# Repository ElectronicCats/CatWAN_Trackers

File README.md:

# LoRa CatTrack Zero

Electronic Cats invests time and resources providing this open source design, please support Electronic Cats and open-source hardware by purchasing products from Electronic Cats!

Designed by Electronic Cats.

Hardware released under an CERN Open Hardware Licence v1.2. See the LICENSE_HARDWARE file for more information.

Electronic Cats is a registered trademark, please do not use if you sell these PCBs.

26 Nov 2018

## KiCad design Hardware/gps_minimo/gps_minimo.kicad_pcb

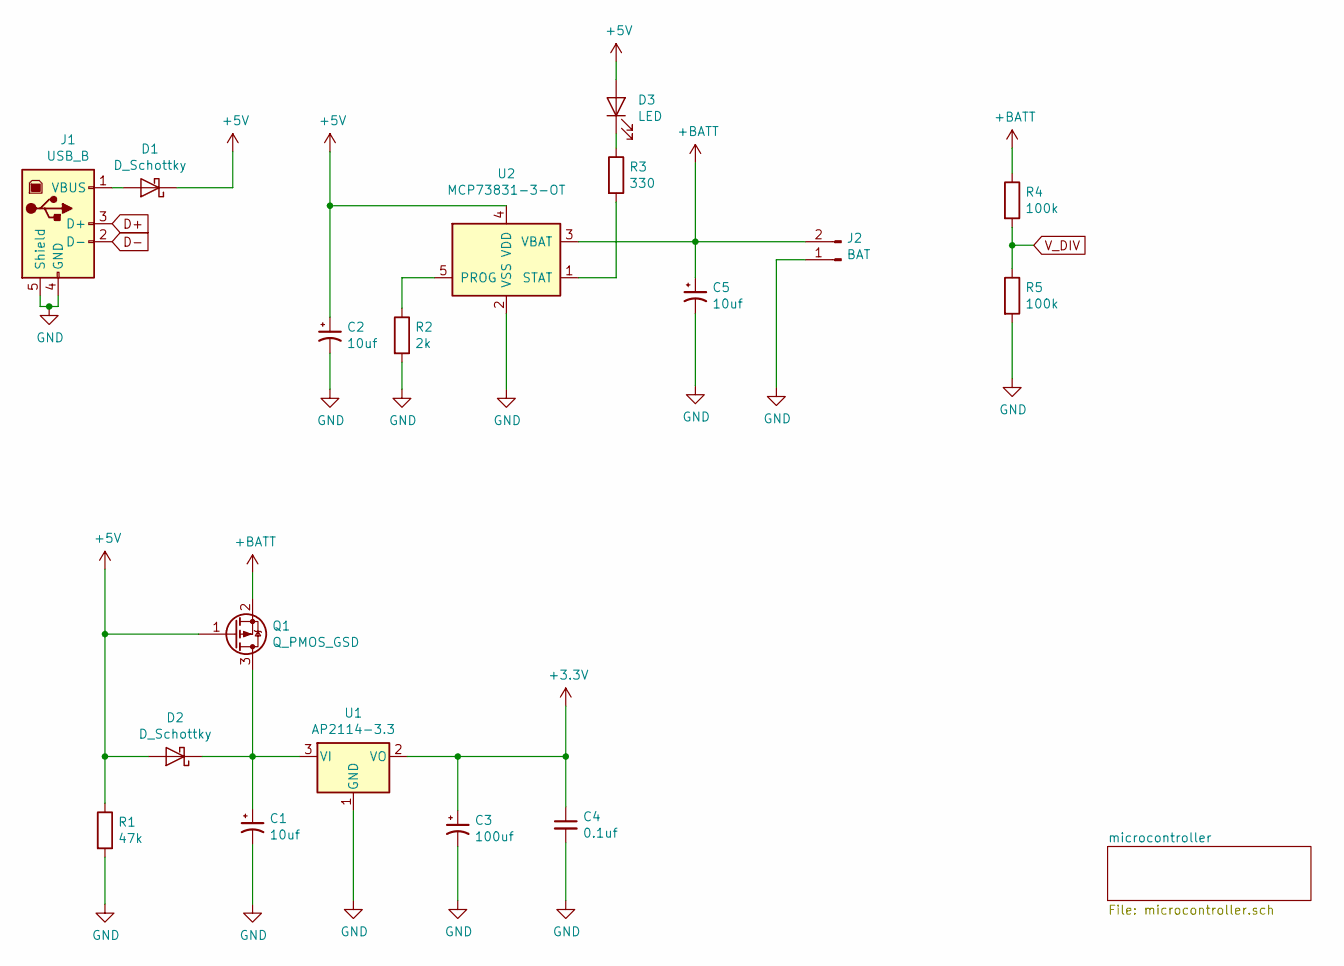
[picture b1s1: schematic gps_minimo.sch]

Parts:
C1, C2, C5: 10uf; C_1206_3216Metric_Pad1.42x1.75mm_HandSolder
C3: 100uf; C_1206_3216Metric_Pad1.42x1.75mm_HandSolder
C4: 0.1uf; C_1206_3216Metric_Pad1.42x1.75mm_HandSolder
D1, D2: D_Schottky; D_SOD-123
D3: LED; LED_1206_3216Metric_Pad1.42x1.75mm_HandSolder
J1: USB_B; USB_Micro-B_Wuerth_629105150521
J2: BAT; PinHeader_1x02_P2.54mm_Vertical
Q1: Q_PMOS_GSD; SOT-23
R1: 47k; R_1206_3216Metric_Pad1.42x1.75mm_HandSolder
R2: 2k; R_1206_3216Metric_Pad1.42x1.75mm_HandSolder
R3: 330; R_1206_3216Metric_Pad1.42x1.75mm_HandSolder
R4, R5: 100k; R_1206_3216Metric_Pad1.42x1.75mm_HandSolder
U1: AP2114-3.3; SOT-223-3_TabPin2
U2: MCP73831-3-OT; SOT-23-5

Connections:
+3V3: C3.1, C4.1, U1.2 (VO); also elsewhere on the board
+5V: C2.1, D1.1 (K), D2.2 (A), D3.2 (A), Q1.1 (G), R1.1, U2.4 (VDD)
+BATT: C5.1, J2.2, Q1.2 (S), R4.1, U2.3 (VBAT)
D+: J1.3 (D+); also elsewhere on the board
D-: J1.2 (D-); also elsewhere on the board
GND: C1.2, C2.2, C3.2, C4.2, C5.2, J1.4 (GND), J1.5 (Shield), J2.1, R1.2, R2.2, R5.2, U1.1 (GND), U2.2 (VSS); also elsewhere on the board
unnamed: C1.1, D2.1 (K), Q1.3 (D), U1.3 (VI)
unnamed: D1.2 (A), J1.1 (VBUS)
unnamed: D3.1 (K), R3.1
unnamed: R2.1, U2.5 (PROG)
unnamed: R3.2, U2.1 (STAT)
V_DIV: R4.2, R5.1; also elsewhere on the board

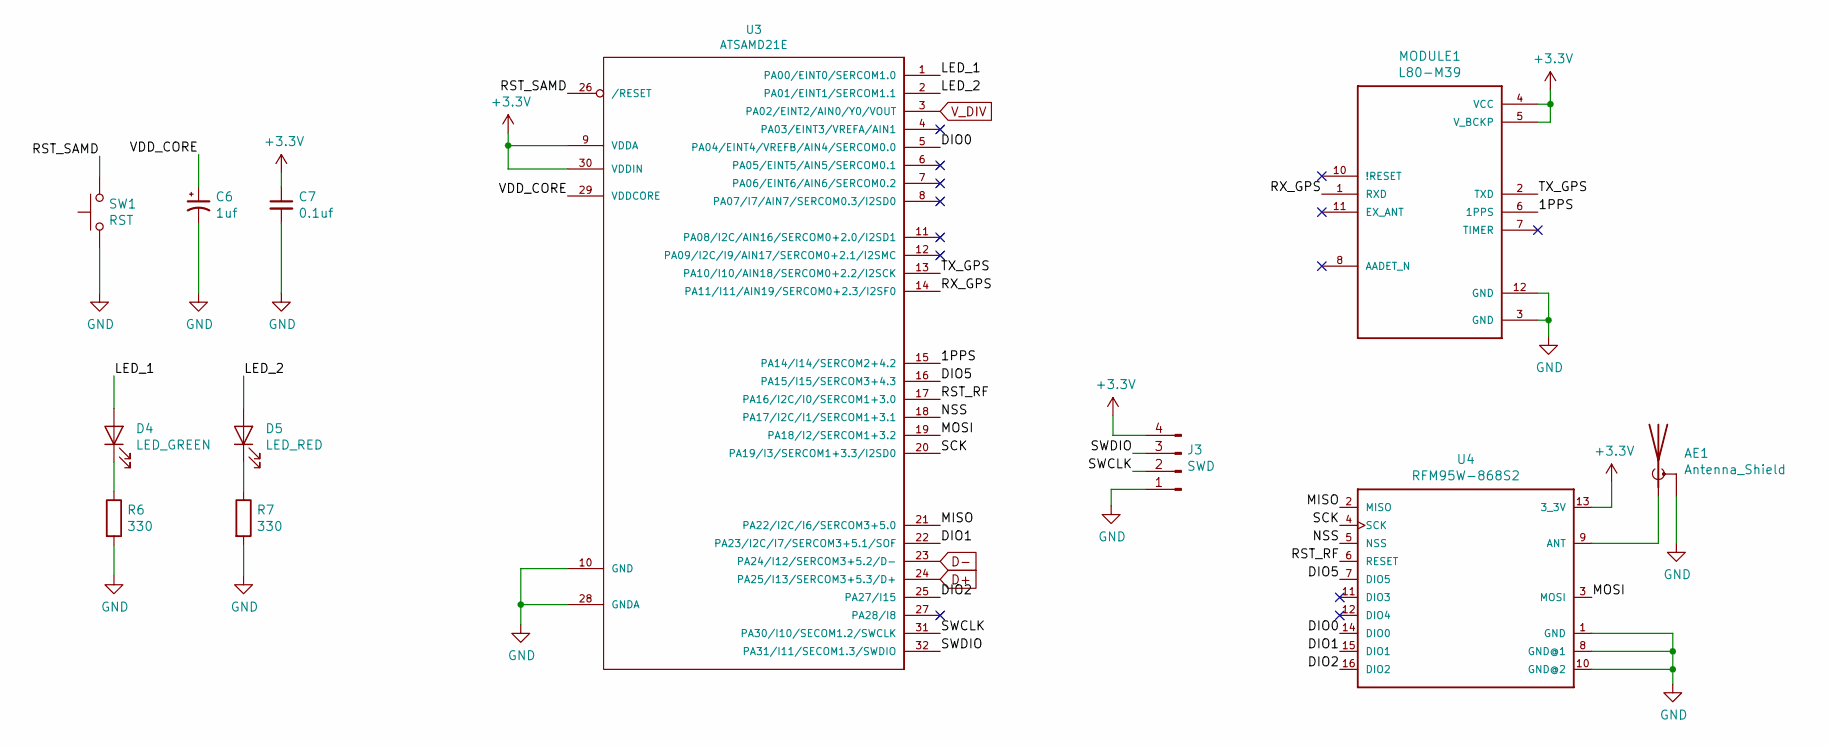
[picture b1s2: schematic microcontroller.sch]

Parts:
AE1: Antenna_Shield; MOLEX_1661
C6: 1uf; C_1206_3216Metric_Pad1.42x1.75mm_HandSolder
C7: 0.1uf; C_1206_3216Metric_Pad1.42x1.75mm_HandSolder
D4: LED_GREEN; LED_1206_3216Metric_Castellated
D5: LED_RED; LED_1206_3216Metric_Castellated
J3: SWD; PinHeader_1x04_P2.54mm_Vertical
MODULE1: L80-M39; QUECTEL_L80-M39
R6, R7: 330; R_1206_3216Metric_Pad1.42x1.75mm_HandSolder
SW1: RST; SW_SPST_TL3342
U3: ATSAMD21E; TQFP-32_7x7mm_P0.8mm
U4: RFM95W-868S2; RFM95W

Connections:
+3V3: C7.1, J3.4, MODULE1.4 (VCC), MODULE1.5 (V_BCKP), U3.9 (VDDA), U3.30 (VDDIN), U4.13 (3_3V); also elsewhere on the board
/microcontroller/1PPS: MODULE1.6 (1PPS), U3.15 (PA14/I14/SERCOM2+4.2)
/microcontroller/DIO0: U3.5 (PA04/EINT4/VREFB/AIN4/SERCOM0.0), U4.14 (DIO0)
/microcontroller/DIO1: U3.22 (PA23/I2C/I7/SERCOM3+5.1/SOF), U4.15 (DIO1)
/microcontroller/DIO2: U3.25 (PA27/I15), U4.16 (DIO2)
/microcontroller/DIO5: U3.16 (PA15/I15/SERCOM3+4.3), U4.7 (DIO5)
/microcontroller/LED_1: D4.2 (A), U3.1 (PA00/EINT0/SERCOM1.0)
/microcontroller/LED_2: D5.2 (A), U3.2 (PA01/EINT1/SERCOM1.1)
/microcontroller/MISO: U3.21 (PA22/I2C/I6/SERCOM3+5.0), U4.2 (MISO)
/microcontroller/MOSI: U3.19 (PA18/I2/SERCOM1+3.2), U4.3 (MOSI)
/microcontroller/NSS: U3.18 (PA17/I2C/I1/SERCOM1+3.1), U4.5 (NSS)
/microcontroller/RST_RF: U3.17 (PA16/I2C/I0/SERCOM1+3.0), U4.6 (RESET)
/microcontroller/RST_SAMD: SW1.2, U3.26 (/RESET)
/microcontroller/RX_GPS: MODULE1.1 (RXD), U3.14 (PA11/I11/AIN19/SERCOM0+2.3/I2SF0)
/microcontroller/SCK: U3.20 (PA19/I3/SERCOM1+3.3/I2SD0), U4.4 (SCK)
/microcontroller/SWCLK: J3.2, U3.31 (PA30/I10/SECOM1.2/SWCLK)
/microcontroller/SWDIO: J3.3, U3.32 (PA31/I11/SECOM1.3/SWDIO)
/microcontroller/TX_GPS: MODULE1.2 (TXD), U3.13 (PA10/I10/AIN18/SERCOM0+2.2/I2SCK)
/microcontroller/VDD_CORE: C6.1, U3.29 (VDDCORE)
D+: U3.24 (PA25/I13/SERCOM3+5.3/D+); also elsewhere on the board
D-: U3.23 (PA24/I12/SERCOM3+5.2/D-); also elsewhere on the board
GND: AE1.2 (Shield), C6.2, C7.2, J3.1, MODULE1.3 (GND), MODULE1.12 (GND), R6.2, R7.2, SW1.1, U3.10 (GND), U3.28 (GNDA), U4.1 (GND), U4.8 (GND@1), U4.10 (GND@2); also elsewhere on the board
unnamed: AE1.1 (A), U4.9 (ANT)
unnamed: D4.1 (K), R6.1
unnamed: D5.1 (K), R7.1
V_DIV: U3.3 (PA02/EINT2/AIN0/Y0/VOUT); also elsewhere on the board

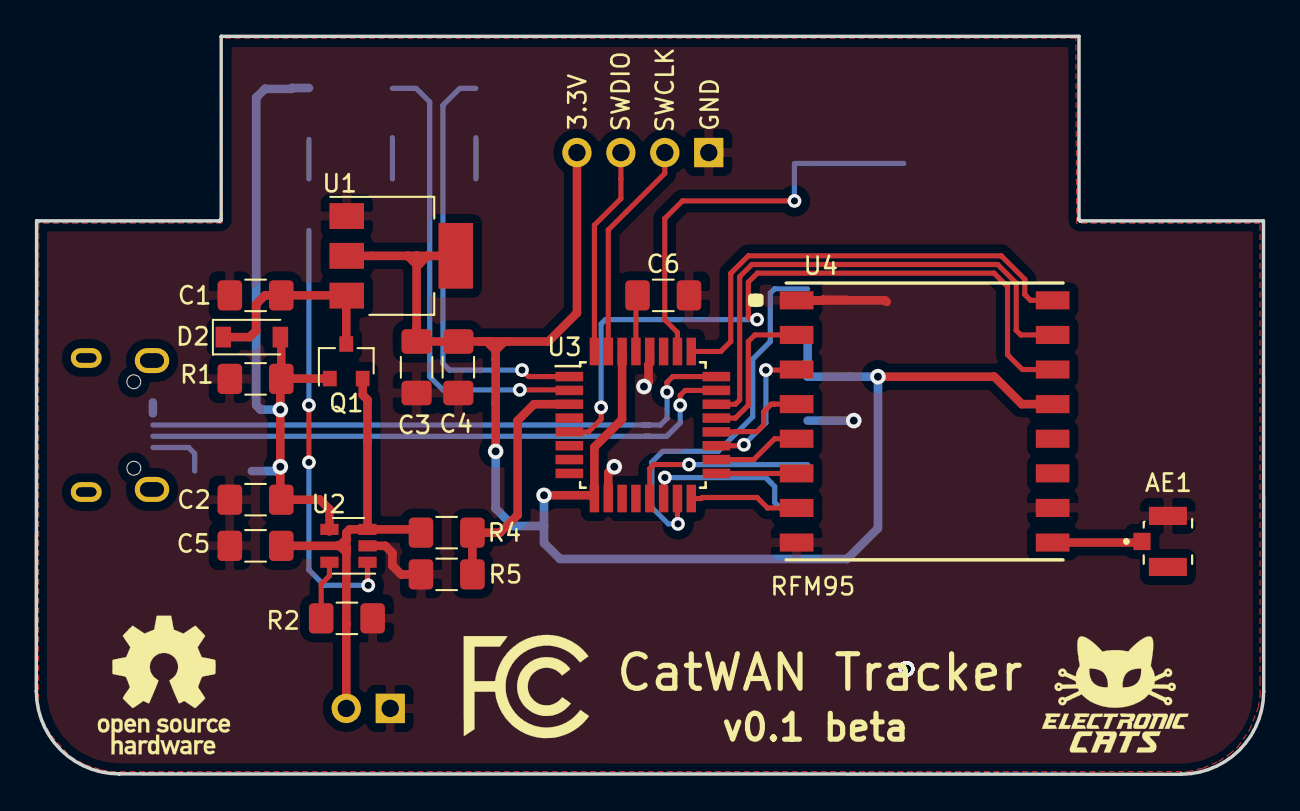
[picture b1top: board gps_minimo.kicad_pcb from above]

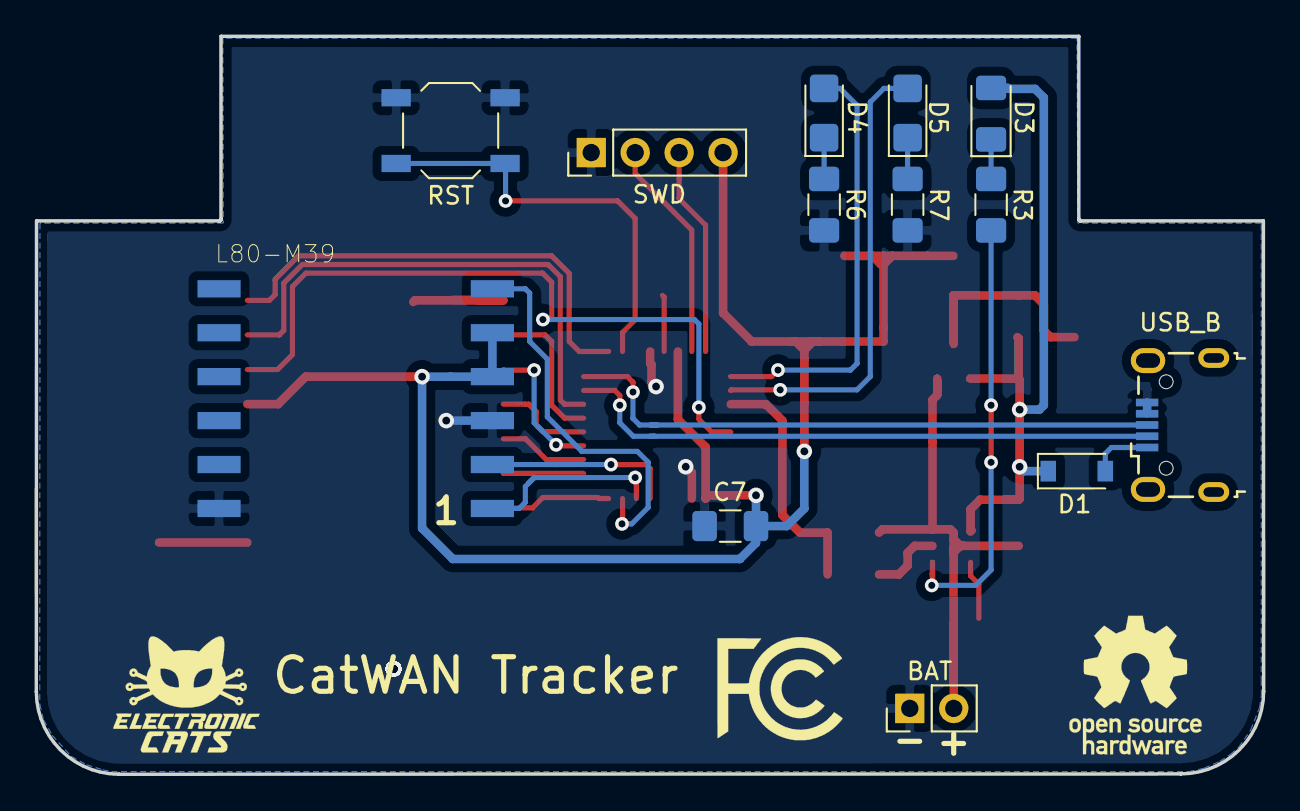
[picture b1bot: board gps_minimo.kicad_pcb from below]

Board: 2 copper layers, 71.0 x 42.7 mm, 30 parts (13 on the bottom side), 33 nets.

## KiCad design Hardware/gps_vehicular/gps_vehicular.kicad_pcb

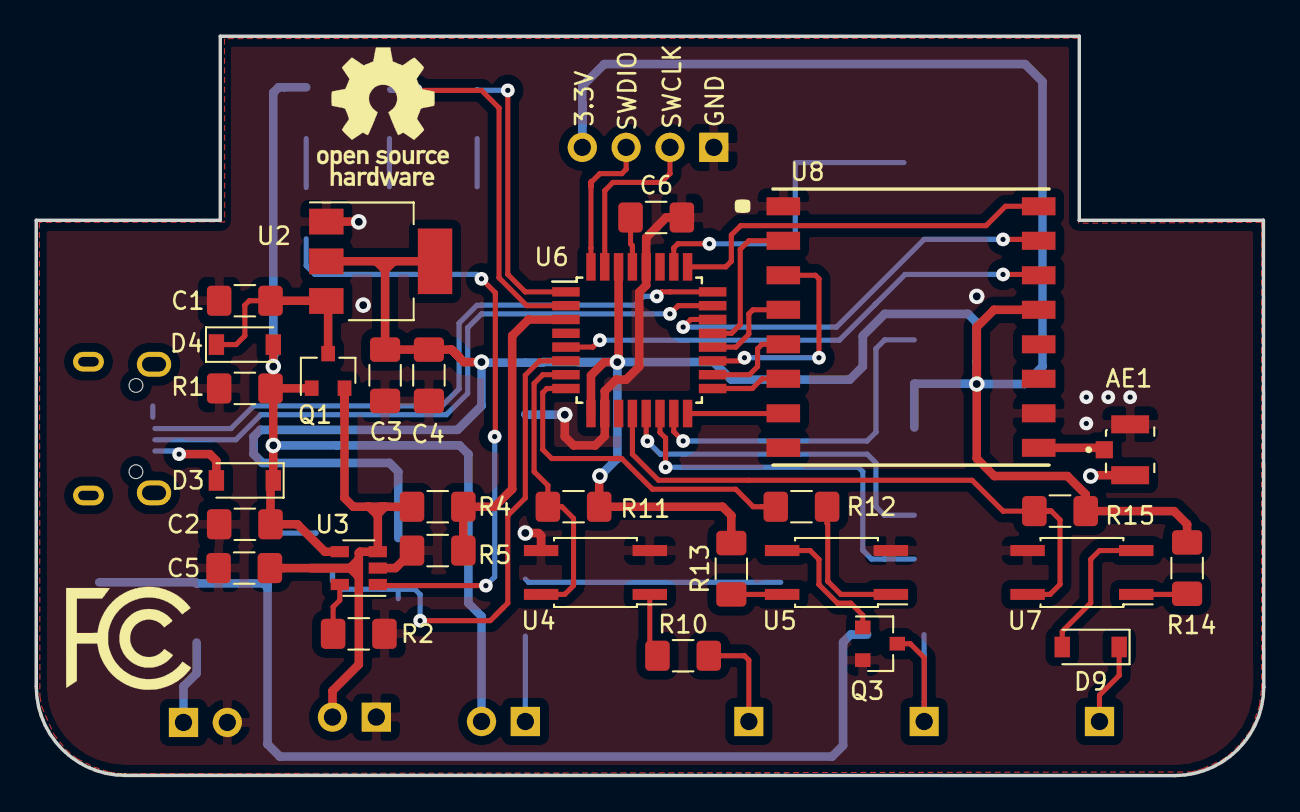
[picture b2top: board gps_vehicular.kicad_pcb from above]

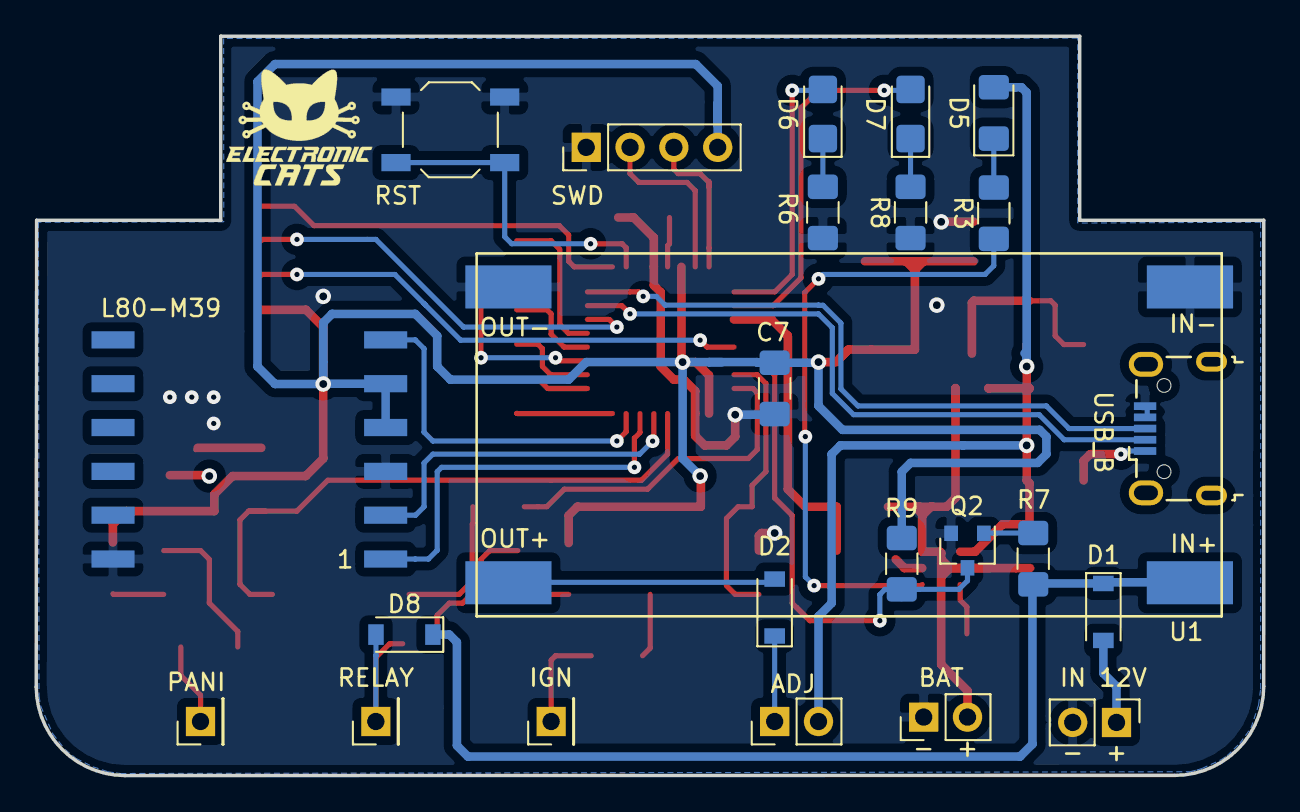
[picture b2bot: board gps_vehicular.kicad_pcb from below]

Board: 2 copper layers, 71.1 x 42.8 mm, 53 parts (24 on the bottom side), 51 nets.

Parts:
AE1: Antenna_Shield; MOLEX_1661
C1, C2, C5: 10uf; C_1206_3216Metric_Pad1.42x1.75mm_HandSolder
C3: 100uf; C_1206_3216Metric_Pad1.42x1.75mm_HandSolder
C4, C7: 0.1uf; C_1206_3216Metric_Pad1.42x1.75mm_HandSolder
C6: 1uf; C_1206_3216Metric_Pad1.42x1.75mm_HandSolder
D1, D2, D3, D4, D8, D9: D_Schottky; D_SOD-123
D5: LED; LED_1206_3216Metric_Pad1.42x1.75mm_HandSolder
D6: LED_GREEN; LED_1206_3216Metric_Castellated
D7: LED_RED; LED_1206_3216Metric_Castellated
J1: IN 12V; PinHeader_1x02_P2.54mm_Vertical
J2: USB_B; USB_Micro-B_Wuerth_629105150521
J3: ADJ; PinHeader_1x02_P2.54mm_Vertical
J4: BAT; PinHeader_1x02_P2.54mm_Vertical
J5: IGN; PinHeader_1x01_P2.54mm_Vertical
J6: RELAY; PinHeader_1x01_P2.54mm_Vertical
J7: PANI; PinHeader_1x01_P2.54mm_Vertical
J8: SWD; PinHeader_1x04_P2.54mm_Vertical
MODULE1: L80-M39; QUECTEL_L80-M39
Q1: Q_PMOS_GSD; SOT-23
Q2, Q3: SMMBT3904LT1G; SOT-23
R1: 47k; R_1206_3216Metric_Pad1.42x1.75mm_HandSolder
R2: 2k; R_1206_3216Metric_Pad1.42x1.75mm_HandSolder
R3, R6, R8, R12, R14: 330; R_1206_3216Metric_Pad1.42x1.75mm_HandSolder
R4, R5: 100k; R_1206_3216Metric_Pad1.42x1.75mm_HandSolder
R7, R10, R13: 1k; R_1206_3216Metric_Pad1.42x1.75mm_HandSolder
R9, R11, R15: 10k; R_1206_3216Metric_Pad1.42x1.75mm_HandSolder
SW1: RST; SW_SPST_TL3342
U1: LM2596; LM2596DC-DC
U2: AP2114-3.3; SOT-223-3_TabPin2
U3: MCP73831-3-OT; SOT-23-5
U4, U5, U7: LTV-352T; SO-4_4.4x3.6mm_P2.54mm
U6: ATSAMD21E; TQFP-32_7x7mm_P0.8mm
U8: RFM95W-868S2; RFM95W

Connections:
+3V3: C3.1, C4.1, C7.1, J8.4, MODULE1.4, MODULE1.5, R9.2, R11.2, R13.2, R14.2, R15.2, U2.2, U6.9, U6.30, U8.13
+5V: C2.1, D3.1, D4.2, D5.2, J3.2, Q1.1, R1.1, U3.4
+12V: D1.1, D8.1, R7.2, U1.1
+BATT: C5.1, J4.2, Q1.2, R4.1, U3.3
/microcontroller/1PPS: MODULE1.6, U6.15
/microcontroller/DIO0: U6.5, U8.14
/microcontroller/DIO1: U6.22, U8.15
/microcontroller/DIO2: U6.25, U8.16
/microcontroller/DIO5: U6.16, U8.7
/microcontroller/LED_1: D6.2, U6.1
/microcontroller/LED_2: D7.2, U6.2
/microcontroller/MISO: U6.21, U8.2
/microcontroller/MOSI: U6.19, U8.3
/microcontroller/NSS: U6.18, U8.5
/microcontroller/OUT_SIG: R12.2, U6.8
/microcontroller/RST_RF: U6.17, U8.6
/microcontroller/RST_SAMD: SW1.2, U6.26
/microcontroller/RX_GPS: MODULE1.1, U6.14
/microcontroller/SCK: U6.20, U8.4
/microcontroller/SIG_CONECTADO: Q2.3, R9.1, U6.6
/microcontroller/SIG_IGNI: R11.1, U4.4, U6.7
/microcontroller/SIG_PANI: R15.1, U6.12, U7.4
/microcontroller/SWCLK: J8.2, U6.31
/microcontroller/SWDIO: J8.3, U6.32
/microcontroller/TX_GPS: MODULE1.2, U6.13
/microcontroller/VDD_CORE: C6.1, U6.29
D+: J2.3, U6.24
D-: J2.2, U6.23
GND: AE1.2, C1.2, C2.2, C3.2, C4.2, C5.2, C6.2, C7.2, J1.2, J2.4, J2.5, J4.1, J8.1, MODULE1.3, MODULE1.12, Q2.2, Q3.2, R1.2, R2.2, R5.2, R6.2, R8.2, SW1.1, U1.2, U1.4, U2.1, U3.2, U4.2, U4.3, U5.2, U6.10, U6.28, U7.3, U8.1, U8.8, U8.10
unnamed: AE1.1, U8.9
unnamed: C1.1, D4.1, Q1.3, U2.3
unnamed: D1.2, J1.1
unnamed: D2.1, J3.1
unnamed: D2.2, U1.3
unnamed: D3.2, J2.1
unnamed: D5.1, R3.1
unnamed: D6.1, R6.1
unnamed: D7.1, R8.1
unnamed: D8.2, J6.1, Q3.3
unnamed: D9.1, J7.1
unnamed: D9.2, U7.2
unnamed: J5.1, R10.2
unnamed: Q2.1, R7.1
unnamed: Q3.1, U5.3
unnamed: R2.1, U3.5
unnamed: R3.2, U3.1
unnamed: R10.1, U4.1
unnamed: R12.1, U5.1
unnamed: R13.1, U5.4
unnamed: R14.1, U7.1
V_DIV: R4.2, R5.1, U6.3

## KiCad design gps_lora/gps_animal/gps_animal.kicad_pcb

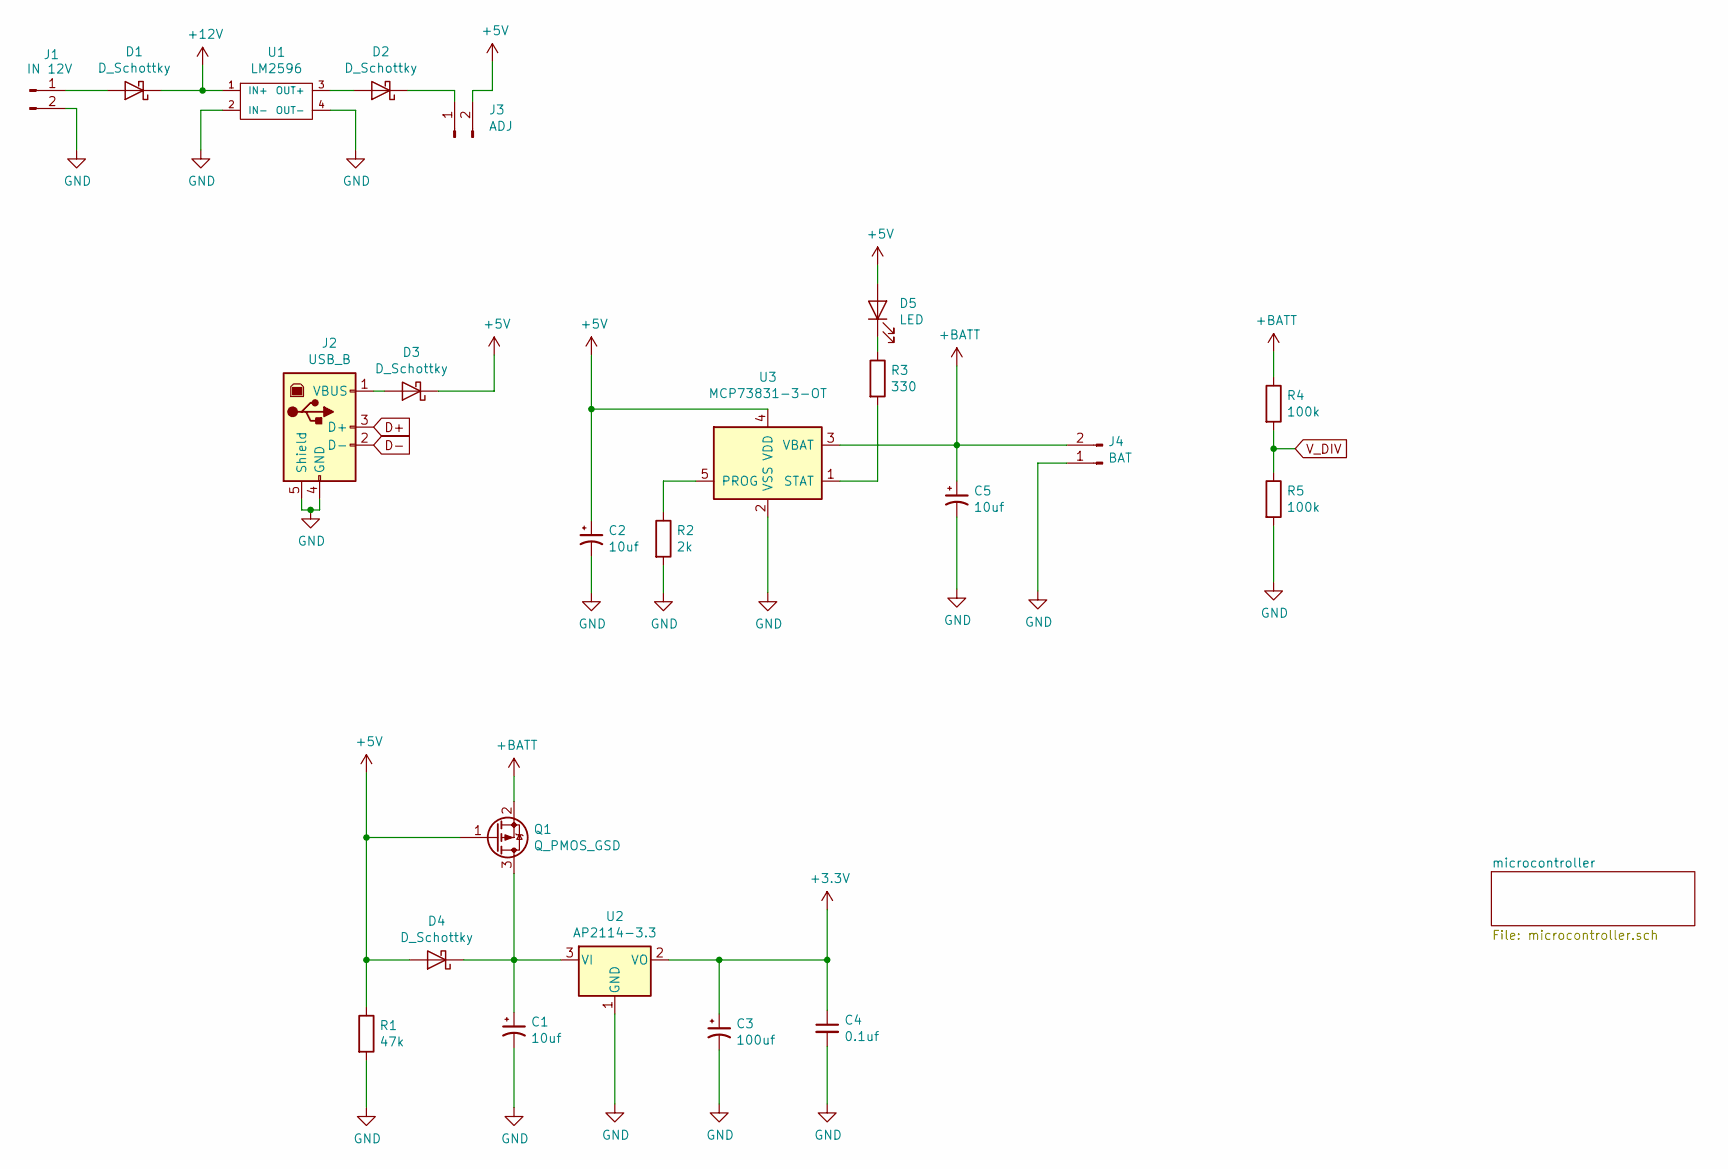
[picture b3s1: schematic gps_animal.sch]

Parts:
C1, C2, C5: 10uf; C_1206_3216Metric_Pad1.42x1.75mm_HandSolder
C3: 100uf; C_1206_3216Metric_Pad1.42x1.75mm_HandSolder
C4: 0.1uf; C_1206_3216Metric_Pad1.42x1.75mm_HandSolder
D1, D2, D3, D4: D_Schottky; D_SOD-123
D5: LED; LED_1206_3216Metric_Pad1.42x1.75mm_HandSolder
J1: IN 12V; PinHeader_1x02_P2.54mm_Vertical
J2: USB_B; USB_Micro-B_Wuerth_629105150521
J3: ADJ; PinHeader_1x02_P2.54mm_Vertical
J4: BAT; PinHeader_1x02_P2.54mm_Vertical
Q1: Q_PMOS_GSD; SOT-23
R1: 47k; R_1206_3216Metric_Pad1.42x1.75mm_HandSolder
R2: 2k; R_1206_3216Metric_Pad1.42x1.75mm_HandSolder
R3: 330; R_1206_3216Metric_Pad1.42x1.75mm_HandSolder
R4, R5: 100k; R_1206_3216Metric_Pad1.42x1.75mm_HandSolder
U1: LM2596; LM2596DC-DC
U2: AP2114-3.3; SOT-223-3_TabPin2
U3: MCP73831-3-OT; SOT-23-5

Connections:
+3V3: C3.1, C4.1, U2.2 (VO); also elsewhere on the board
+5V: C2.1, D3.1 (K), D4.2 (A), D5.2 (A), J3.2, Q1.1 (G), R1.1, U3.4 (VDD)
+12V: D1.1 (K), U1.1 (IN+); also elsewhere on the board
+BATT: C5.1, J4.2, Q1.2 (S), R4.1, U3.3 (VBAT)
D+: J2.3 (D+); also elsewhere on the board
D-: J2.2 (D-); also elsewhere on the board
GND: C1.2, C2.2, C3.2, C4.2, C5.2, J1.2, J2.4 (GND), J2.5 (Shield), J4.1, R1.2, R2.2, R5.2, U1.2 (IN-), U1.4 (OUT-), U2.1 (GND), U3.2 (VSS); also elsewhere on the board
unnamed: C1.1, D4.1 (K), Q1.3 (D), U2.3 (VI)
unnamed: D1.2 (A), J1.1
unnamed: D2.1 (K), J3.1
unnamed: D2.2 (A), U1.3 (OUT+)
unnamed: D3.2 (A), J2.1 (VBUS)
unnamed: D5.1 (K), R3.1
unnamed: R2.1, U3.5 (PROG)
unnamed: R3.2, U3.1 (STAT)
V_DIV: R4.2, R5.1

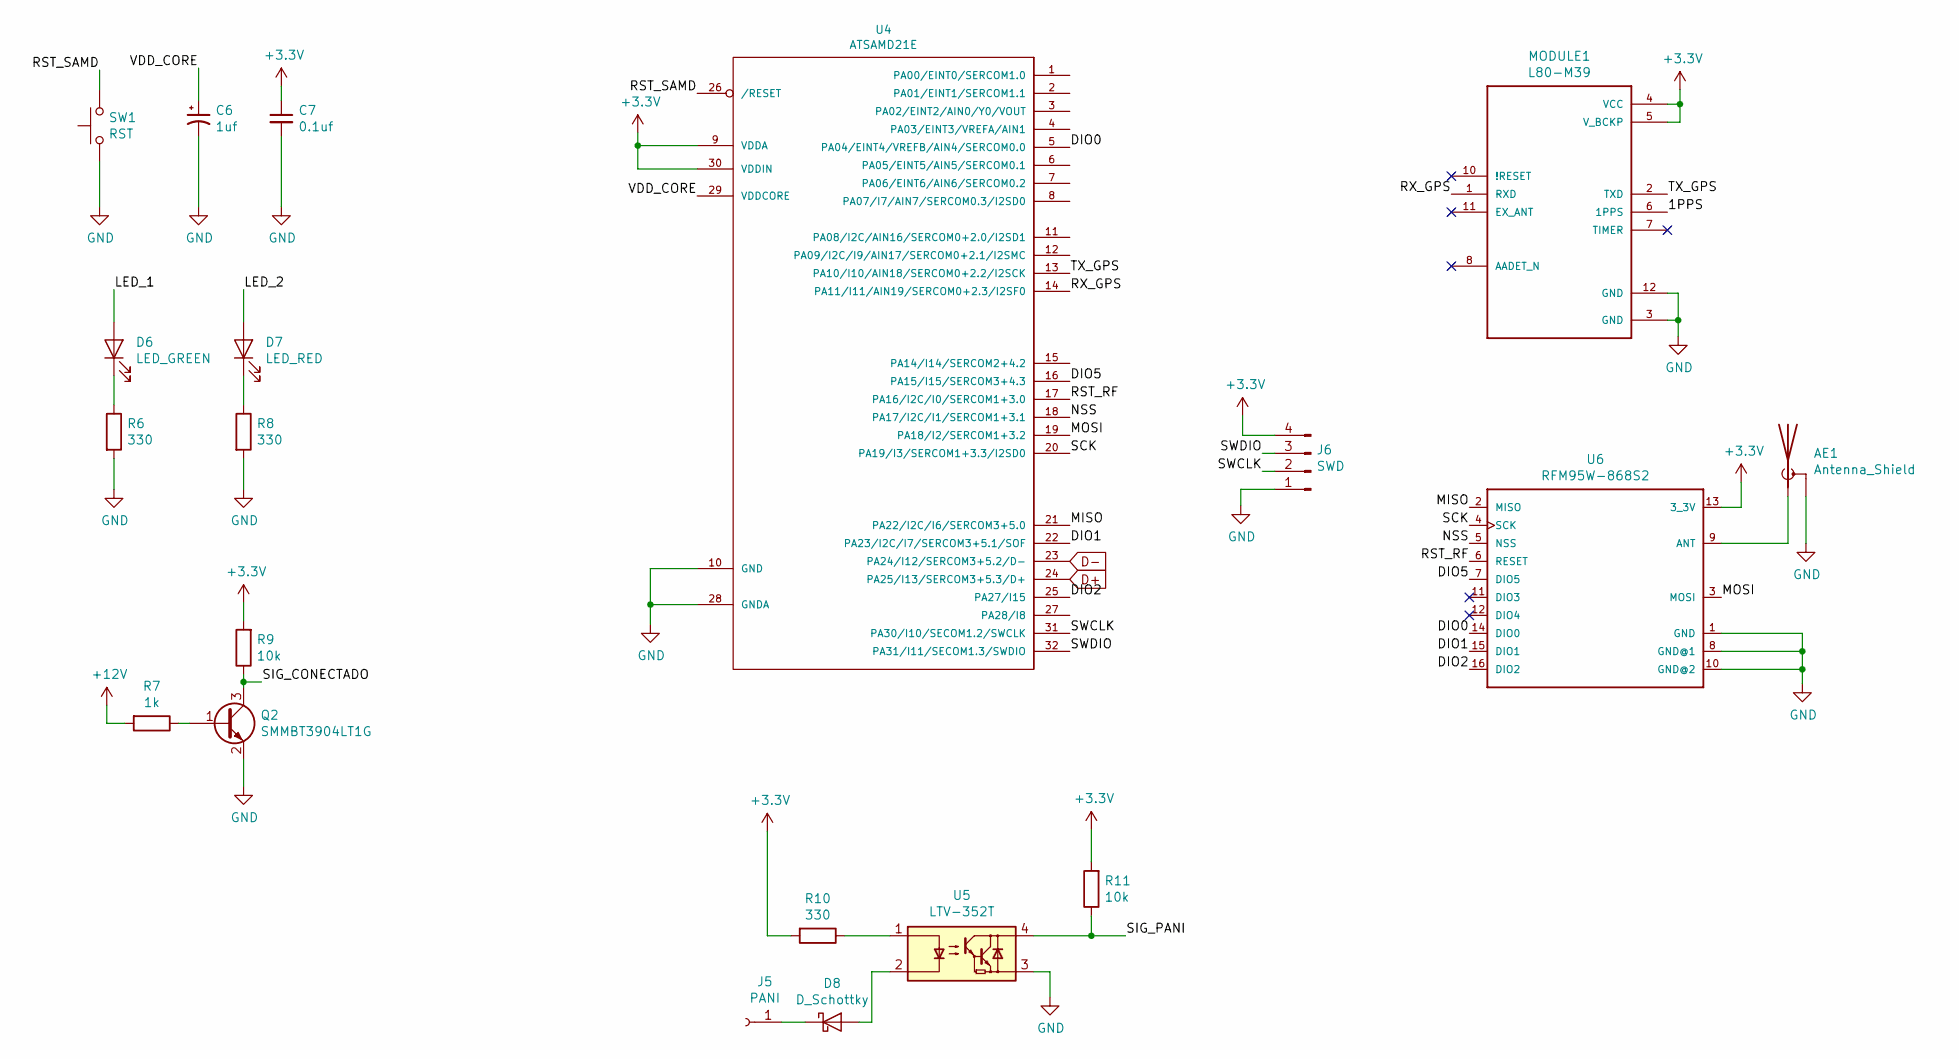
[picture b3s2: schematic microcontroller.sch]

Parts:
AE1: Antenna_Shield; MOLEX_1661
C6: 1uf; C_1206_3216Metric_Pad1.42x1.75mm_HandSolder
C7: 0.1uf; C_1206_3216Metric_Pad1.42x1.75mm_HandSolder
D6: LED_GREEN; LED_1206_3216Metric_Castellated
D7: LED_RED; LED_1206_3216Metric_Castellated
D8: D_Schottky; D_SOD-123
J5: PANI; PinHeader_1x01_P2.54mm_Vertical
J6: SWD; PinHeader_1x04_P2.54mm_Vertical
MODULE1: L80-M39; QUECTEL_L80-M39
Q2: SMMBT3904LT1G; SOT-23
R6, R8, R10: 330; R_1206_3216Metric_Pad1.42x1.75mm_HandSolder
R7: 1k; R_1206_3216Metric_Pad1.42x1.75mm_HandSolder
R9, R11: 10k; R_1206_3216Metric_Pad1.42x1.75mm_HandSolder
SW1: RST; SW_SPST_TL3342
U4: ATSAMD21E; TQFP-32_7x7mm_P0.8mm
U5: LTV-352T; SO-4_4.4x3.6mm_P2.54mm
U6: RFM95W-868S2; RFM95W

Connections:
+3V3: C7.1, J6.4, MODULE1.4 (VCC), MODULE1.5 (V_BCKP), R9.2, R10.2, R11.2, U4.9 (VDDA), U4.30 (VDDIN), U6.13 (3_3V); also elsewhere on the board
+12V: R7.2; also elsewhere on the board
/microcontroller/1PPS: MODULE1.6 (1PPS)
/microcontroller/DIO0: U4.5 (PA04/EINT4/VREFB/AIN4/SERCOM0.0), U6.14 (DIO0)
/microcontroller/DIO1: U4.22 (PA23/I2C/I7/SERCOM3+5.1/SOF), U6.15 (DIO1)
/microcontroller/DIO2: U4.25 (PA27/I15), U6.16 (DIO2)
/microcontroller/DIO5: U4.16 (PA15/I15/SERCOM3+4.3), U6.7 (DIO5)
/microcontroller/LED_1: D6.2 (A)
/microcontroller/LED_2: D7.2 (A)
/microcontroller/MISO: U4.21 (PA22/I2C/I6/SERCOM3+5.0), U6.2 (MISO)
/microcontroller/MOSI: U4.19 (PA18/I2/SERCOM1+3.2), U6.3 (MOSI)
/microcontroller/NSS: U4.18 (PA17/I2C/I1/SERCOM1+3.1), U6.5 (NSS)
/microcontroller/RST_RF: U4.17 (PA16/I2C/I0/SERCOM1+3.0), U6.6 (RESET)
/microcontroller/RST_SAMD: SW1.2, U4.26 (/RESET)
/microcontroller/RX_GPS: MODULE1.1 (RXD), U4.14 (PA11/I11/AIN19/SERCOM0+2.3/I2SF0)
/microcontroller/SCK: U4.20 (PA19/I3/SERCOM1+3.3/I2SD0), U6.4 (SCK)
/microcontroller/SIG_CONECTADO: Q2.3 (C), R9.1
/microcontroller/SIG_PANI: R11.1, U5.4
/microcontroller/SWCLK: J6.2, U4.31 (PA30/I10/SECOM1.2/SWCLK)
/microcontroller/SWDIO: J6.3, U4.32 (PA31/I11/SECOM1.3/SWDIO)
/microcontroller/TX_GPS: MODULE1.2 (TXD), U4.13 (PA10/I10/AIN18/SERCOM0+2.2/I2SCK)
/microcontroller/VDD_CORE: C6.1, U4.29 (VDDCORE)
D+: U4.24 (PA25/I13/SERCOM3+5.3/D+); also elsewhere on the board
D-: U4.23 (PA24/I12/SERCOM3+5.2/D-); also elsewhere on the board
GND: AE1.2 (Shield), C6.2, C7.2, J6.1, MODULE1.3 (GND), MODULE1.12 (GND), Q2.2 (E), R6.2, R8.2, SW1.1, U4.10 (GND), U4.28 (GNDA), U5.3, U6.1 (GND), U6.8 (GND@1), U6.10 (GND@2); also elsewhere on the board
unnamed: AE1.1 (A), U6.9 (ANT)
unnamed: D6.1 (K), R6.1
unnamed: D7.1 (K), R8.1
unnamed: D8.1 (K), J5.1
unnamed: D8.2 (A), U5.2
unnamed: Q2.1 (B), R7.1
unnamed: R10.1, U5.1

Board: 2 copper layers, 43 parts (0 on the bottom side), 40 nets, no tracks yet.

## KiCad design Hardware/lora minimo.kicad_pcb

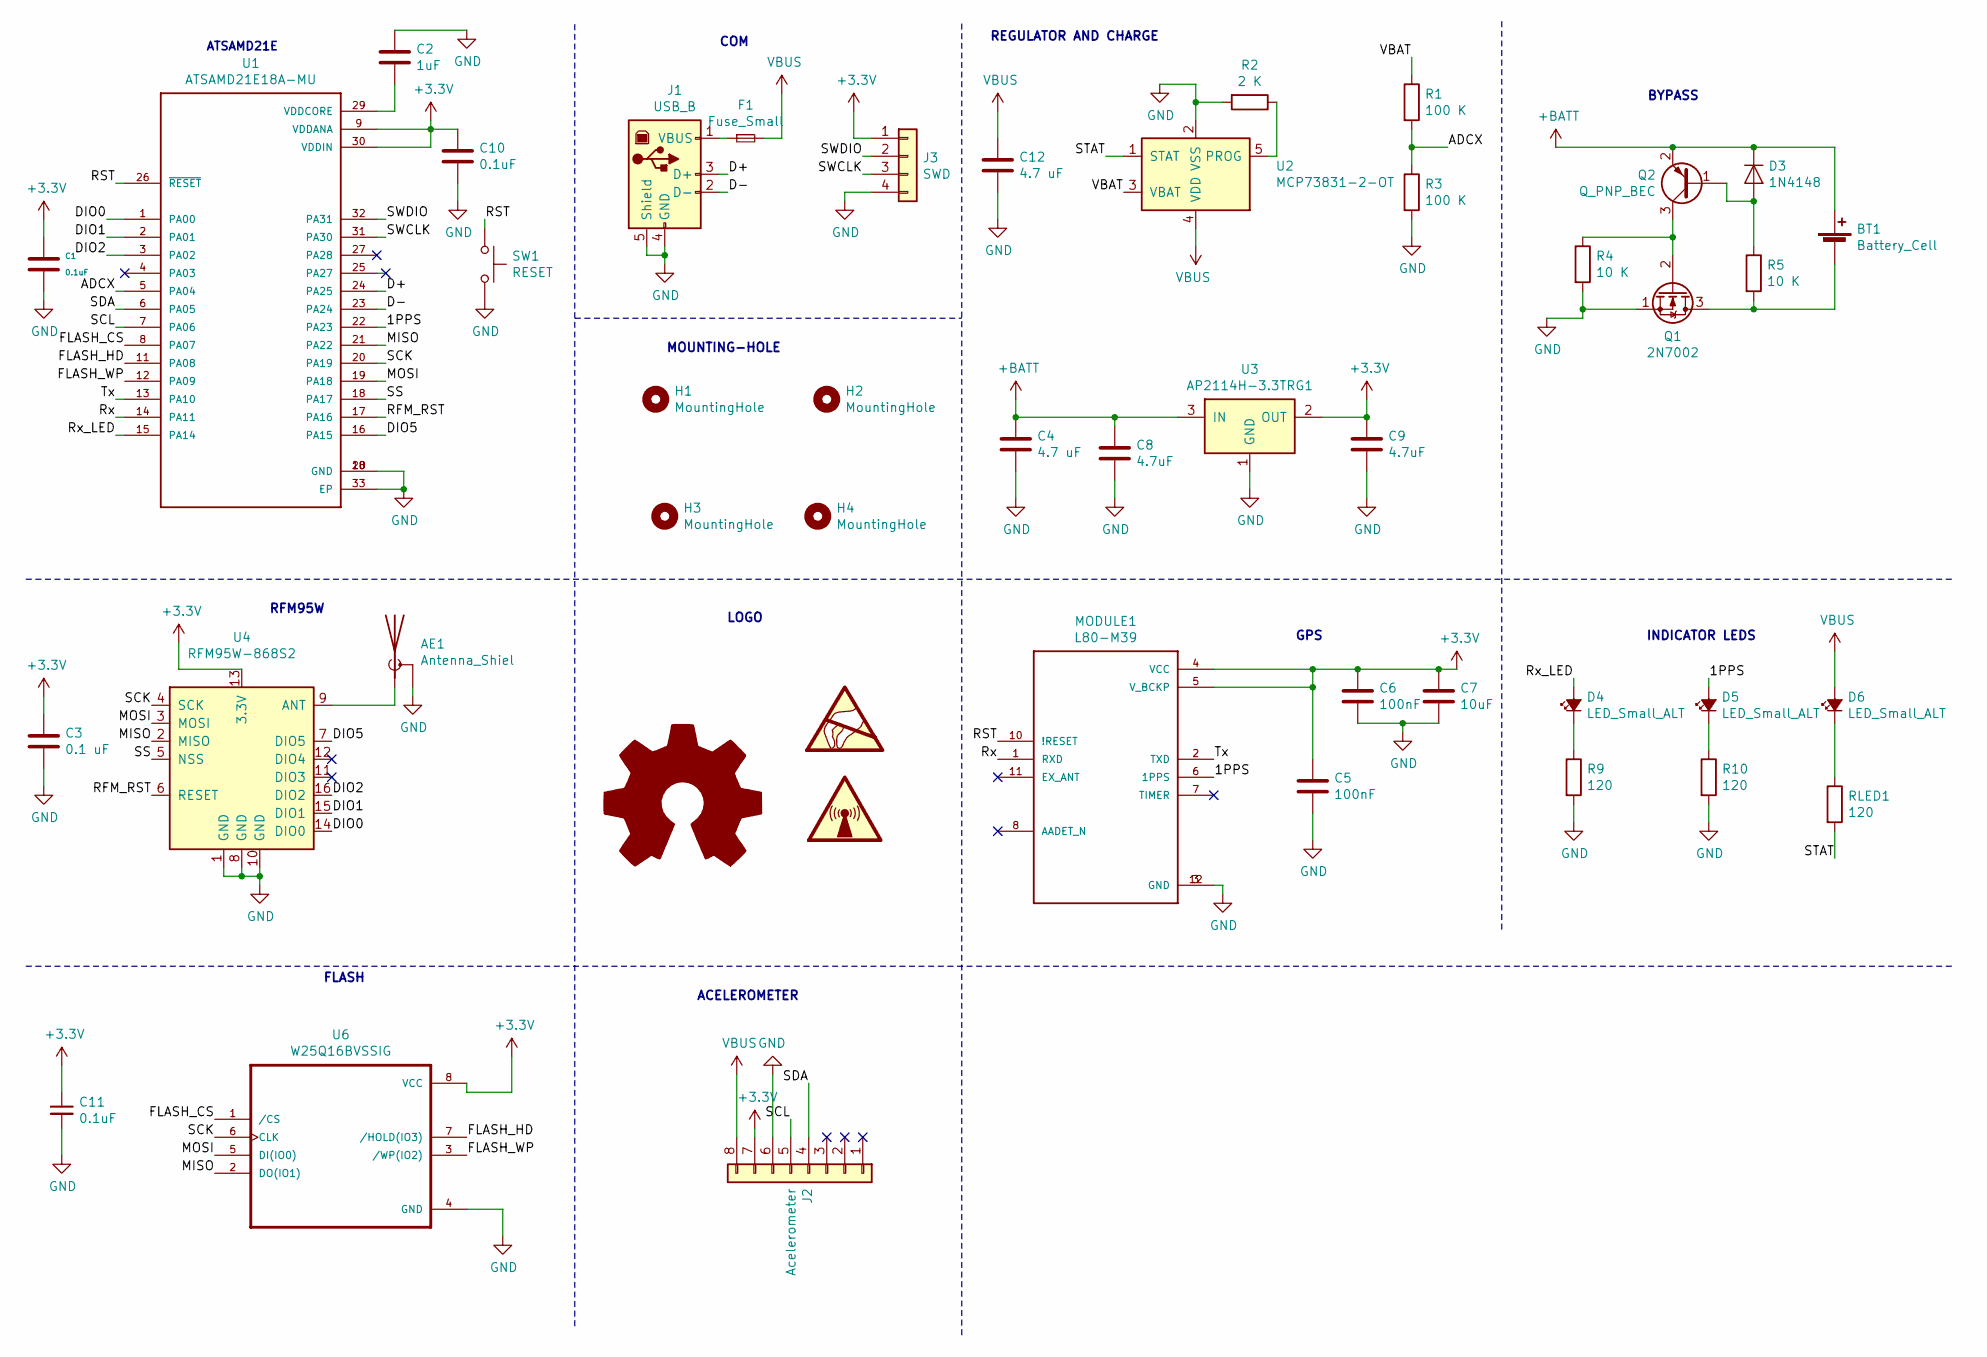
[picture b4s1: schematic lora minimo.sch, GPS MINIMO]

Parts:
AE1: Antenna_Shiel; AMPHENOL_901-144
BT1: Battery_Cell; BAT-HLD-012-SMT-OTL
C1, C10, C11: 0.1uF; C_0805_HandSoldering
C2: 1uF; C_0805_HandSoldering
C3: 0.1 uF; C_0805_HandSoldering
C4, C12: 4.7 uF; C_0805_HandSoldering
C5, C6: 100nF; C_0805_HandSoldering
C7: 10uF; C_0805_HandSoldering
C8, C9: 4.7uF; C_0805_HandSoldering
D3: 1N4148; D_SOD-323_HandSoldering
D4, D5, D6: LED_Small_ALT; LED_0805_HandSoldering
F1: Fuse_Small; R_1812_HandSoldering
H1, H2, H3, H4: MountingHole; MountingHole_5.3mm_M5_Pad_Via
J1: USB_B; 629105150521
J2: Acelerometer; Pin_Header_Straight_1x08_Pitch2.54mm
J3: SWD; Pin_Header_Straight_2x02_Pitch2.54mm
MODULE1: L80-M39; QUECTEL_L80-M39
Q1: 2N7002; SOT-23
Q2: Q_PNP_BEC; SOT-23
R1, R3: 100 K; R_0805_HandSoldering
R2: 2 K; R_0805_HandSoldering
R4, R5: 10 K; R_0805_HandSoldering
R9, R10: 120; R_0805_HandSoldering
RLED1: 120; R_0805_HandSoldering
SW1: RESET; SW_SPST_B3U-1000P-B
U1: ATSAMD21E18A-MU; TQFP-32_7x7mm_Pitch0.8mm
U2: MCP73831-2-OT; SOT-23-5_HandSoldering
U3: AP2114H-3.3TRG1; SOT-223-3_TabPin2
U4: RFM95W-868S2; RFM95W
U6: W25Q16BVSSIG; Diodes_PSOP-8

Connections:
+3V3: C1.1, C3.1, C5.1, C6.1, C7.1, C9.1, C10.1, C11.1, J2.7, J3.1, MODULE1.4 (VCC), MODULE1.5 (V_BCKP), U1.9 (VDDANA), U1.30 (VDDIN), U3.2 (OUT), U4.13 (3.3V), U6.8 (VCC)
+BATT: BT1.1 (+), C4.1, C8.1, D3.1 (K), Q2.2 (E), U3.3 (IN)
/1PPS: D5.2 (A), MODULE1.6 (1PPS), U1.22 (PA23)
/ADCX: R1.2, R3.1, U1.5 (PA04)
/D+: J1.3 (D+), U1.24 (PA25)
/D-: J1.2 (D-), U1.23 (PA24)
/DIO0: U1.1 (PA00), U4.14 (DIO0)
/DIO1: U1.2 (PA01), U4.15 (DIO1)
/DIO2: U1.3 (PA02), U4.16 (DIO2)
/DIO5: U1.16 (PA15), U4.7 (DIO5)
/FLASH_CS: U1.8 (PA07), U6.1 (/CS)
/FLASH_HD: U1.11 (PA08), U6.7 (/HOLD(IO3))
/FLASH_WP: U1.12 (PA09), U6.3 (/WP(IO2))
/MISO: U1.21 (PA22), U4.2 (MISO), U6.2 (DO(IO1))
/MOSI: U1.19 (PA18), U4.3 (MOSI), U6.5 (DI(IO0))
/RFM_RST: U1.17 (PA16), U4.6 (RESET)
/RST: MODULE1.10 (!RESET), SW1.1, U1.26 (~RESET~)
/Rx: MODULE1.1 (RXD), U1.14 (PA11)
/Rx_LED: D4.2 (A), U1.15 (PA14)
/SCK: U1.20 (PA19), U4.4 (SCK), U6.6 (CLK)
/SCL: J2.5, U1.7 (PA06)
/SDA: J2.4, U1.6 (PA05)
/SS: U1.18 (PA17), U4.5 (NSS)
/STAT: RLED1.2, U2.1 (STAT)
/SWCLK: J3.3, U1.31 (PA30)
/SWDIO: J3.2, U1.32 (PA31)
/Tx: MODULE1.2 (TXD), U1.13 (PA10)
/VBAT: R1.1, U2.3 (VBAT)
GND: AE1.2 (Shield), C1.2, C2.1, C3.2, C4.2, C5.2, C6.2, C7.2, C8.2, C9.2, C10.2, C11.2, C12.2, J1.4 (GND), J1.5 (Shield), J2.6, J3.4, MODULE1.3 (GND), MODULE1.12 (GND), Q1.1 (S), R2.2, R3.2, R4.2, R9.2, R10.2, SW1.2, U1.10 (GND), U1.28 (GND), U1.33 (EP), U2.2 (VSS), U3.1 (GND), U4.1 (GND), U4.8 (GND), U4.10 (GND), U6.4 (GND)
unnamed: AE1.1 (A), U4.9 (ANT)
unnamed: BT1.2 (-), Q1.3 (D), R5.2
unnamed: C2.2, U1.29 (VDDCORE)
unnamed: D3.2 (A), Q2.1 (B), R5.1
unnamed: D4.1 (K), R9.1
unnamed: D5.1 (K), R10.1
unnamed: D6.1 (K), RLED1.1
unnamed: F1.1, J1.1 (VBUS)
unnamed: Q1.2 (G), Q2.3 (C), R4.1
unnamed: R2.1, U2.5 (PROG)
VBUS: C12.1, D6.2 (A), F1.2, J2.8, U2.4 (VDD)

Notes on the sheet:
ATSAMD21E
RFM95W
GPS
MOUNTING-HOLE
REGULATOR AND CHARGE
BYPASS
ACELEROMETER
LOGO
FLASH
COM
INDICATOR LEDS
